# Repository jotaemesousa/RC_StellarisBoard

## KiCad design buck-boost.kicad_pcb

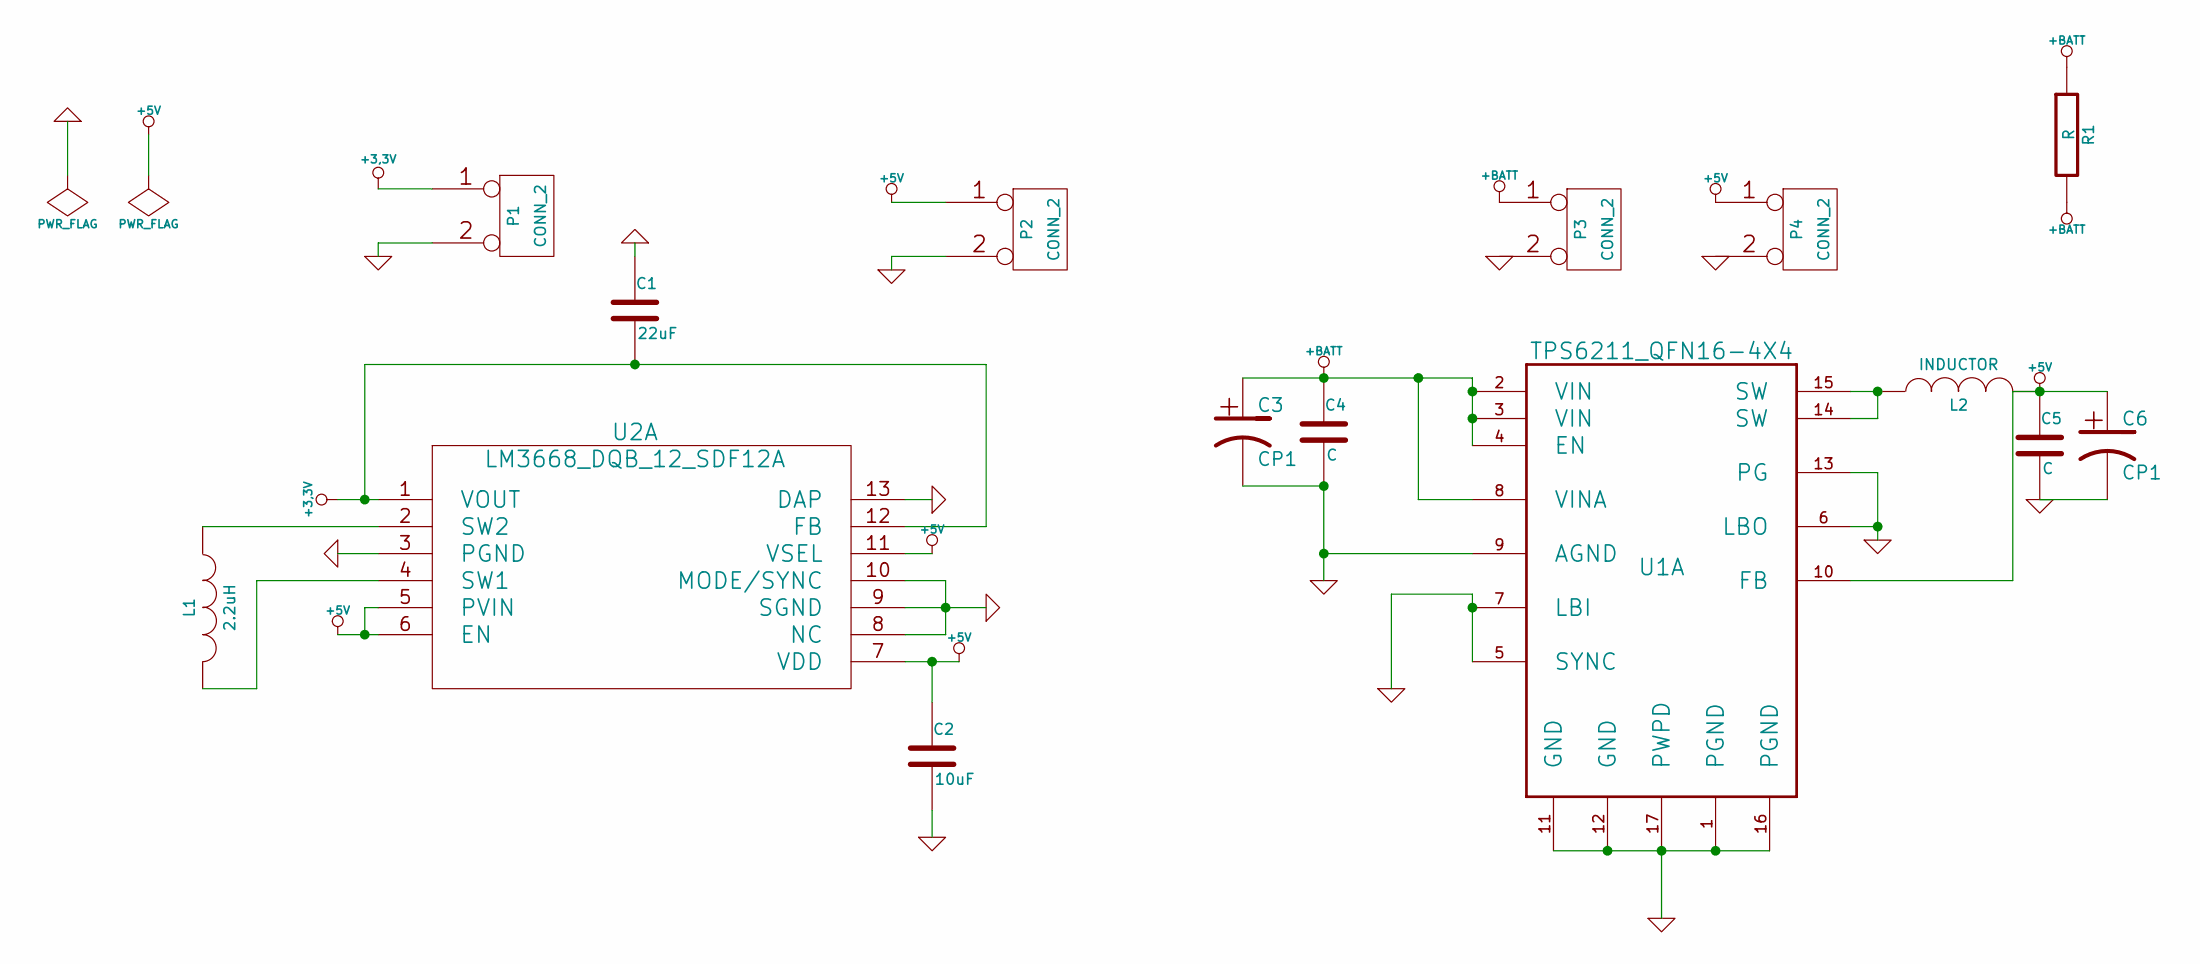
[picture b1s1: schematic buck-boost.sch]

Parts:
C1: 22uF
C2: 10uF
C3, C6: CP1
C4, C5: C
L1: 2.2uH
L2: INDUCTOR
P1, P2, P3, P4: CONN_2
R1: R
U1: TPS6211_QFN16-4X4; QFN16
U2: LM3668_DQB_12_SDF12A

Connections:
+3.3V: C1.2, P1.1, U2.1 (VOUT), U2.12 (FB)
+5V: C2.1, C5.1, C6.1, L2.2, P2.1, P4.1, U1.10 (FB), U2.5 (PVIN), U2.6 (EN), U2.7 (VDD), U2.11 (VSEL)
+BATT: C3.1, C4.1, P3.1, R1.1, R1.2, U1.2 (VIN), U1.3 (VIN), U1.4 (EN), U1.8 (VINA)
GND: C1.1, C2.2, C3.2, C4.2, C5.2, C6.2, P1.2 (PM), P2.2 (PM), P3.2 (PM), P4.2 (PM), U1.1 (PGND), U1.5 (SYNC), U1.6 (LBO), U1.7 (LBI), U1.9 (AGND), U1.11 (GND), U1.12 (GND), U1.13 (PG), U1.16 (PGND), U1.17 (PWPD), U2.3 (PGND), U2.8 (NC), U2.9 (SGND), U2.10 (MODE/SYNC), U2.13 (DAP)
unnamed: L2.1, U1.14 (SW), U1.15 (SW)
unnamed: L1.2, U2.4 (SW1)
unnamed: L1.1, U2.2 (SW2)

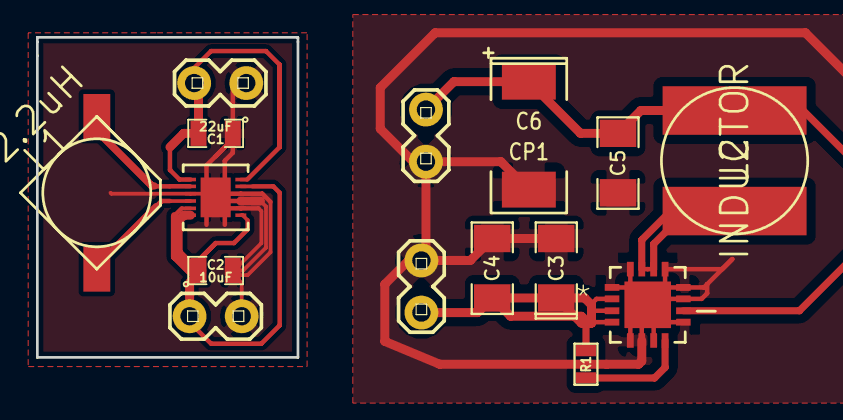
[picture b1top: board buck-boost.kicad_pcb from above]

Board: 2 copper layers, 14.5 x 17.8 mm, 15 parts (0 on the bottom side), 7 nets.

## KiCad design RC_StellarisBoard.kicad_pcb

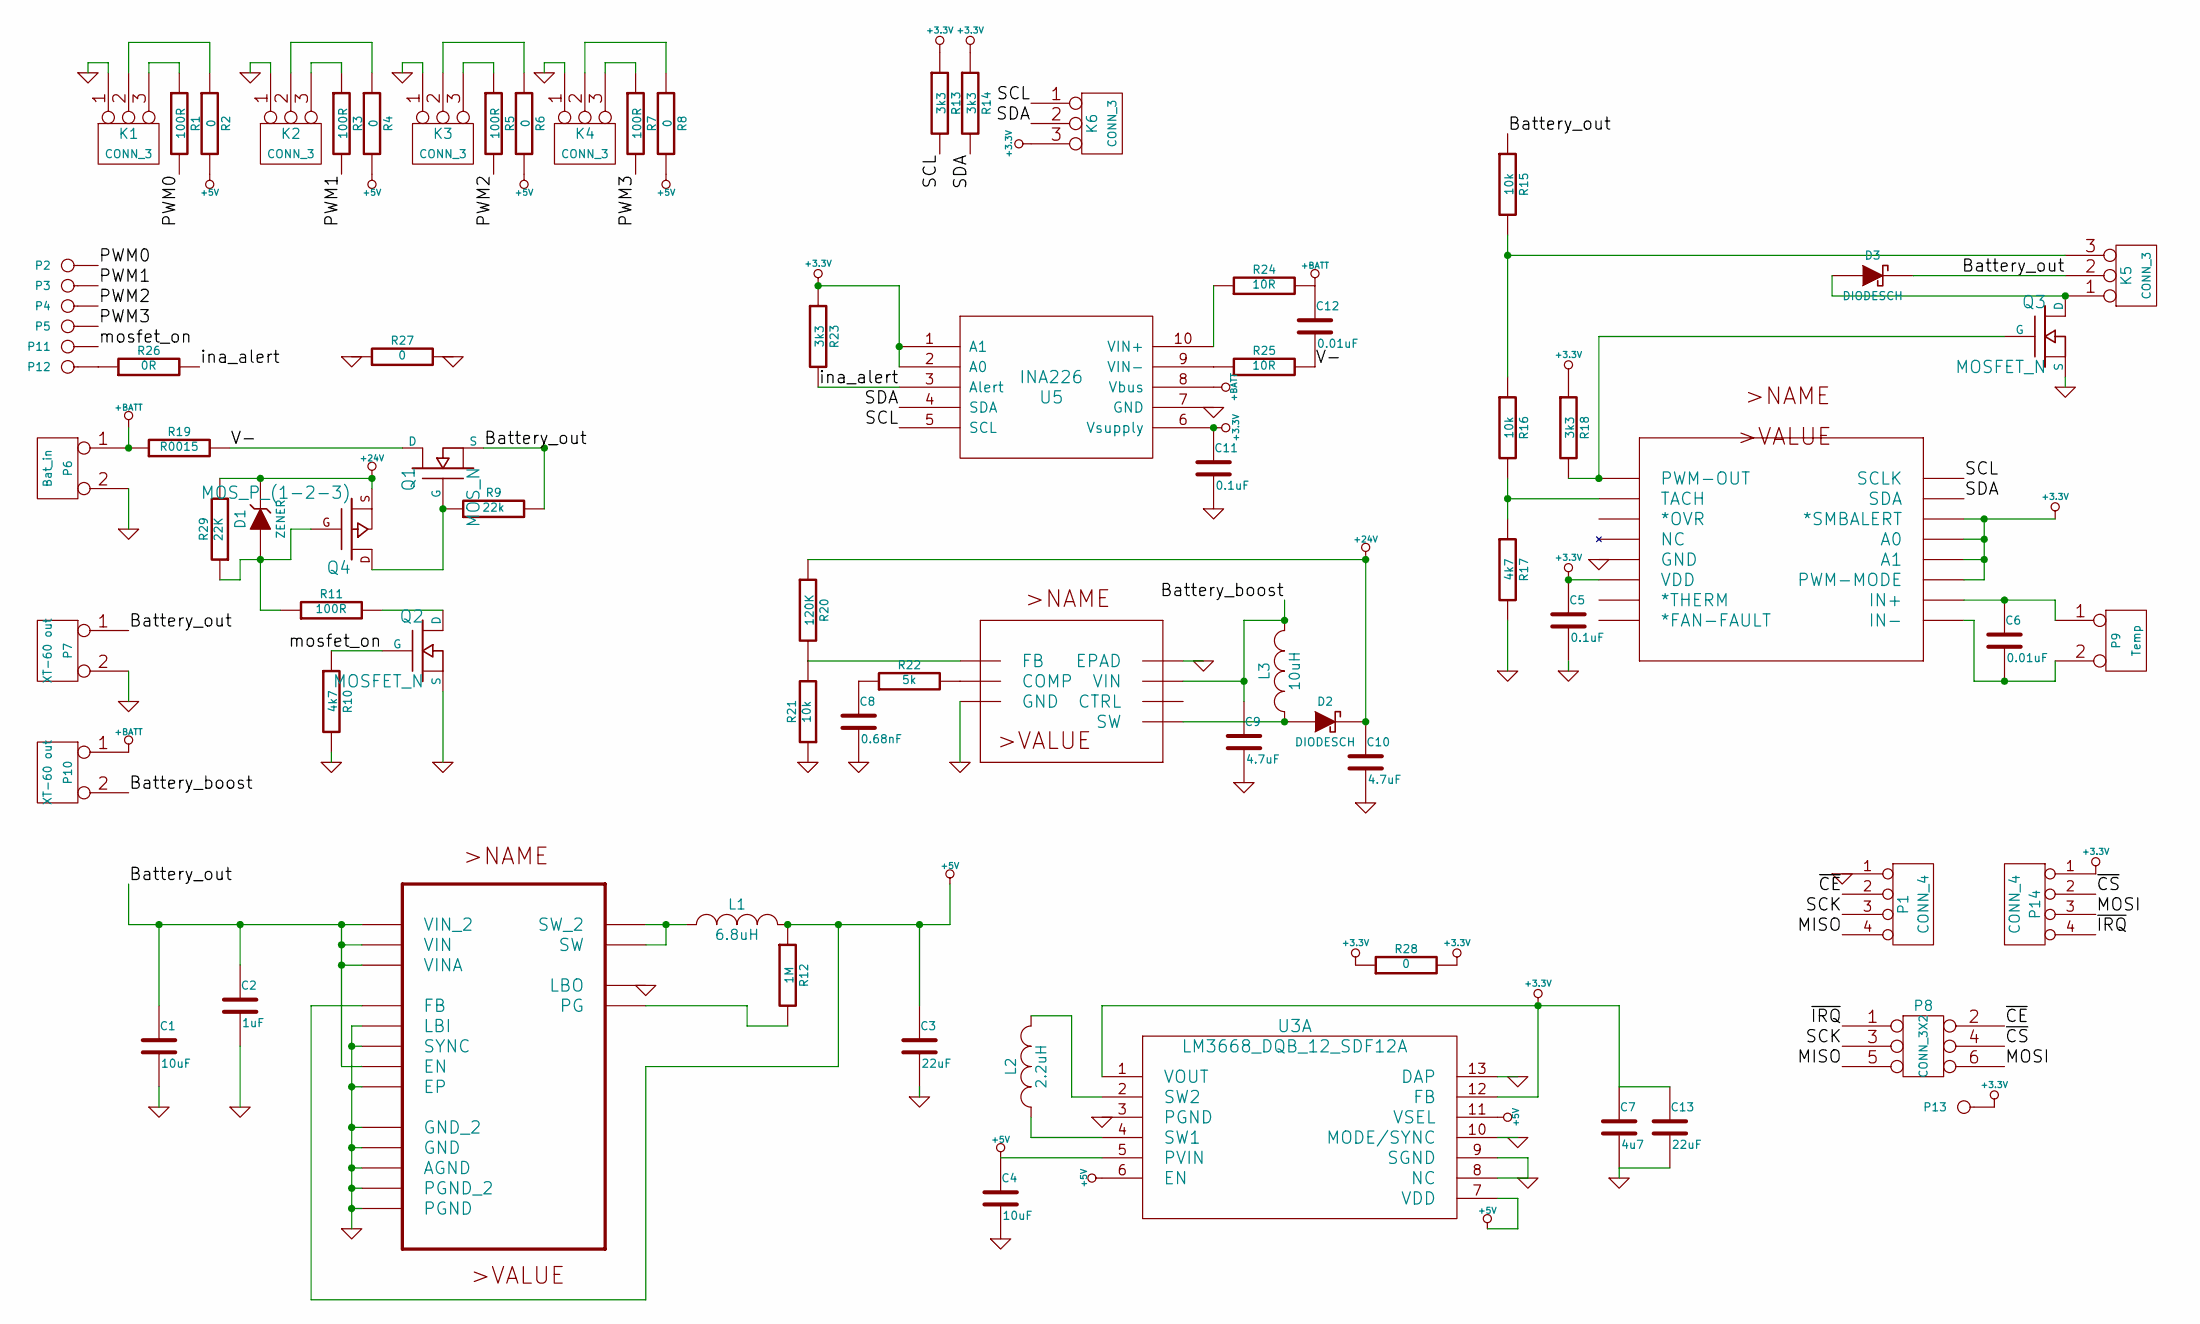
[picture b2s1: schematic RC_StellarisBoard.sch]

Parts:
C1, C4: 10uF
C2: 1uF
C3, C13: 22uF
C5, C11: 0.1uF
C6, C12: 0.01uF
C7: 4u7
C8: 0.68nF
C9, C10: 4.7uF
D1: ZENER
D2, D3: DIODESCH
K1, K2, K3, K4, K5, K6: CONN_3
L1: 6.8uH
L2: 2.2uH
L3: 10uH
P1, P14: CONN_4
P2, P3, P4, P5, P11, P12, P13: CONN_1
P6: Bat_in
P7, P10: XT-60 out
P8: CONN_3X2
P9: Temp
Q1: MOS_N
Q2, Q3: MOSFET_N
Q4: MOS_P_(1-2-3)
R1, R3, R5, R7, R11: 100R
R2, R4, R6, R8: 0
R9: 22k
R10, R17: 4k7
R12: 1M
R13, R14, R18, R23: 3k3
R15, R16, R21: 10k
R19: R0015
R20: 120K
R22: 5k
R24, R25: 10R
R26: 0R
R27, R28: 0
R29: 22K
U1: AMC6821_DBQ_16_DBQ16
U2: TPS62112RSAT_QFN65P400X400X100-17N
U3: LM3668_DQB_12_SDF12A
U4: TPS61170_DRV_6_DRV6_1P6X1
U5: INA226

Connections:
+3.3V: C5.1, C7.1, C11.1, C13.1, K6.3, P13.1, P14.1, R13.1, R14.1, R18.1, R23.1, R28.1, R28.2, U1.6 (VDD), U1.11 (PWM-MODE), U1.12 (A1), U1.13 (A0), U1.14 (*SMBALERT), U3.1 (VOUT), U3.12 (FB), U5.1 (A1), U5.2 (A0), U5.6 (Vsupply)
+5V: C3.1, C4.1, L1.2, R2.2, R4.2, R6.2, R8.2, R12.1, U2.10 (FB), U3.5 (PVIN), U3.6 (EN), U3.7 (VDD), U3.11 (VSEL)
+24V: C10.1, D1.2 (K), D2.2 (K), Q4.S, R20.1, R29.2
+BATT: C12.1, P6.1, P10.1, R19.1, R24.2, U5.8 (Vbus)
/Battery_boost: C9.1, L3.2, P10.2 (PM), U4.6 (VIN)
/Battery_out: C1.1, C2.1, D3.2 (K), K5.2 (PM), P7.1, Q1.S, R9.2, R15.1, U2.2 (VIN_2), U2.3 (VIN), U2.4 (EN), U2.8 (VINA)
/MISO: P1.4, P8.5
/MOSI: P8.6, P14.3
/PWM0: P2.1, R1.2
/PWM1: P3.1, R3.2
/PWM2: P4.1, R5.2
/PWM3: P5.1, R7.2
/SCK: P1.3, P8.3
/SCL: K6.1, R13.2, U1.16 (SCLK), U5.5 (SCL)
/SDA: K6.2 (PM), R14.2, U1.15 (SDA), U5.4 (SDA)
/V-: C12.2, Q1.D, R19.2, R25.2
/ina_alert: R23.2, R26.2, U5.3 (Alert)
/mosfet_on: P11.1, Q2.G, R10.1
/~CE: P1.2, P8.2
/~CS: P8.4, P14.2
/~IRQ: P8.1, P14.4
GND: C1.2, C2.2, C3.2, C4.2, C5.2, C7.2, C8.2, C9.2, C10.2, C11.2, C13.2, K1.1, K2.1, K3.1, K4.1, P1.1, P6.2 (PM), P7.2 (PM), Q2.S, Q3.S, R10.2, R17.2, R21.1, R27.1, R27.2, U1.5 (GND), U2.1 (PGND_2), U2.5 (SYNC), U2.6 (LBO), U2.7 (LBI), U2.9 (AGND), U2.11 (GND_2), U2.12 (GND), U2.16 (PGND), U2.17 (EP), U3.3 (PGND), U3.8 (NC), U3.9 (SGND), U3.10 (MODE/SYNC), U3.13 (DAP), U4.3 (GND), U4.7 (EPAD), U5.7 (GND)
unnamed: K2.2 (PM), R4.1
unnamed: K1.3, R1.1
unnamed: K1.2 (PM), R2.1
unnamed: K2.3, R3.1
unnamed: K3.2 (PM), R6.1
unnamed: K3.3, R5.1
unnamed: D3.1 (A), K5.1, Q3.D
unnamed: L1.1, U2.14 (SW_2), U2.15 (SW)
unnamed: K4.2 (PM), R8.1
unnamed: K4.3, R7.1
unnamed: R25.1, U5.9 (VIN-)
unnamed: P12.1, R26.1
unnamed: R24.1, U5.10 (VIN+)
unnamed: D2.1 (A), L3.1, U4.4 (SW)
unnamed: L2.2, U3.2 (SW2)
unnamed: R20.2, R21.2, U4.1 (FB)
unnamed: D1.1 (A), Q4.G, R11.1, R29.1
unnamed: Q2.D, R11.2
unnamed: Q1.G, Q4.D, R9.1
unnamed: R16.2, R17.1, U1.2 (TACH)
unnamed: K5.3, R15.2, R16.1
unnamed: Q3.G, R18.2, U1.1 (PWM-OUT)
unnamed: L2.1, U3.4 (SW1)
unnamed: R12.2, U2.13 (PG)
unnamed: C8.1, R22.1
unnamed: R22.2, U4.2 (COMP)
unnamed: C6.1, P9.1, U1.10 (IN+)
unnamed: C6.2, P9.2 (PM), U1.9 (IN-)

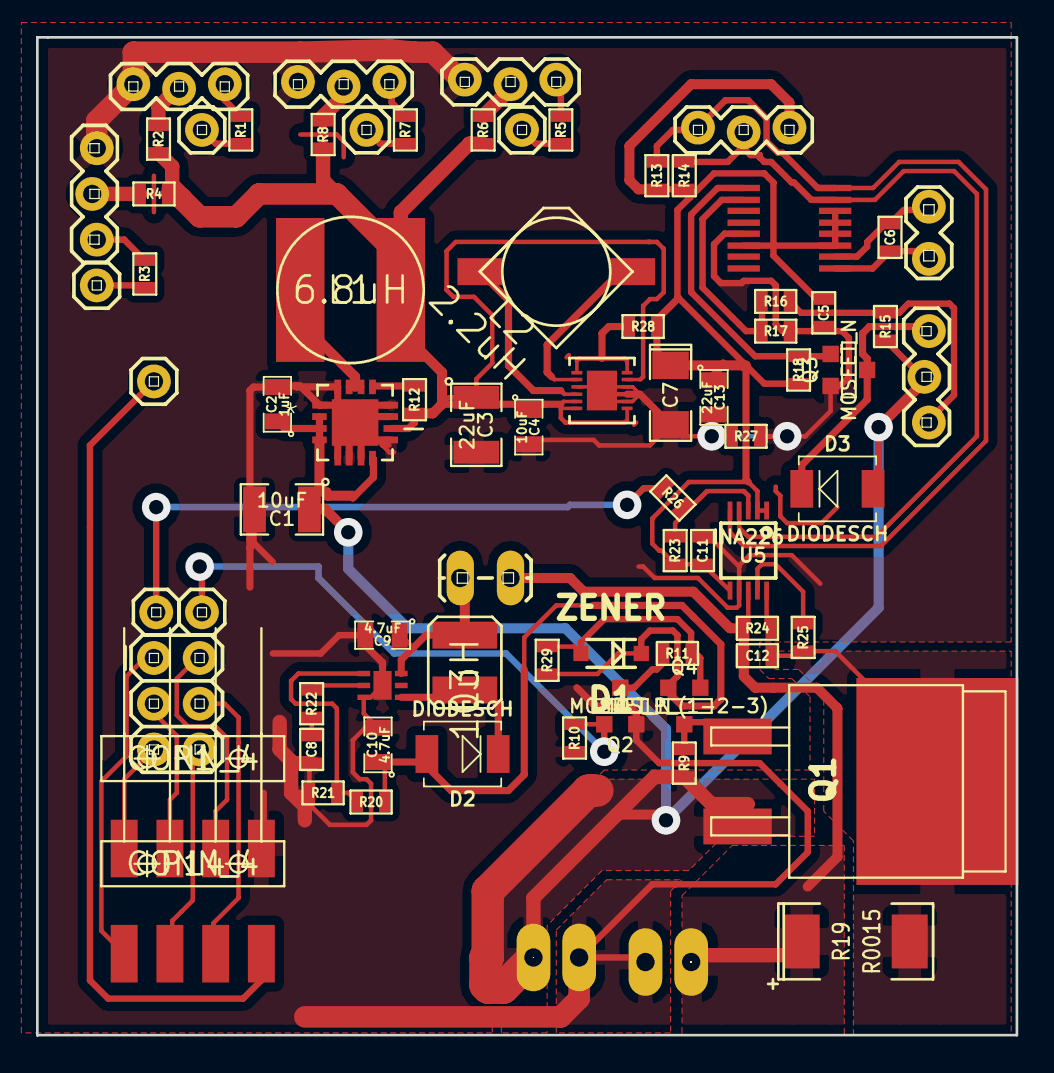
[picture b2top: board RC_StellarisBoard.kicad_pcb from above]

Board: 2 copper layers, 54.4 x 55.4 mm, 77 parts (0 on the bottom side), 50 nets.

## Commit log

2014-01-04 brd + sch
2014-01-05 brd + sch (amc6821 + mosfet)
2014-01-05 versao 1 placa
2014-01-05 versao 1 placa, antes de alterar
2014-01-05 AMC6821 done, amc alterado, conn servo/ESC
2014-01-06 removed roscas-board.brd
2014-01-06 buck boost, DCDC 5 done, servos done
2014-01-06 boost, mosfet + shunt
2014-01-06 boost, mosfet + shunt + board
2014-01-07 falta footprints diodo
2014-01-08 versao com tudo
2014-01-08 v1 completa
2014-01-08 pads
2014-01-09 added nordic
2014-01-09 v3, n confirmado, added fan diode
2014-01-09 corrigido erro buck boost
2014-01-10 first - last
2014-01-10 corrigido erro buck boost 1
2014-01-11 valores
2014-01-11 resist mosfet P done
2014-01-12 valores boost
2014-01-17 feito
